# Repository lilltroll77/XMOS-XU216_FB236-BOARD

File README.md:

# XMOS-XU216_FB236-BOARD
### XMOS XU216-FB236 BOARD made in KiCad
**Current status: In DEVELOPMENT**

A 100 x 100 mm 4 layer PCB based on the XMOS XU216 FB236 chip. PCB can be cascaded during development with full JTAG support, and then be used as a galvanic isolated network without JTAG.\
[Schematic as pdf](https://github.com/lilltroll77/XMOS-XU216_FB236-BOARD/blob/master/XMOS_XUF216_FB236.pdf)

The wrl file is a Virtual reality modeling language file of the board with components. 
It can be opened in [FreeCad](https://www.freecadweb.org/) with hardware acceleration. 
Software rendereing is not recommended for realtime view.
The parts for the PCB are stored in the shapes3D folder.

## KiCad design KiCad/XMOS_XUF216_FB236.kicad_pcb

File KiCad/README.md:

The library for the board should be included in the file XMOS_XUF216_FB236-cache.lib\
To view all 3D parts, you might need to add an alias in the KiCad "3D Search Path Configuration" window\
Alias = vrml\
Path = The path to the shapes3D folder on your local machine. (After you have cloned this project)

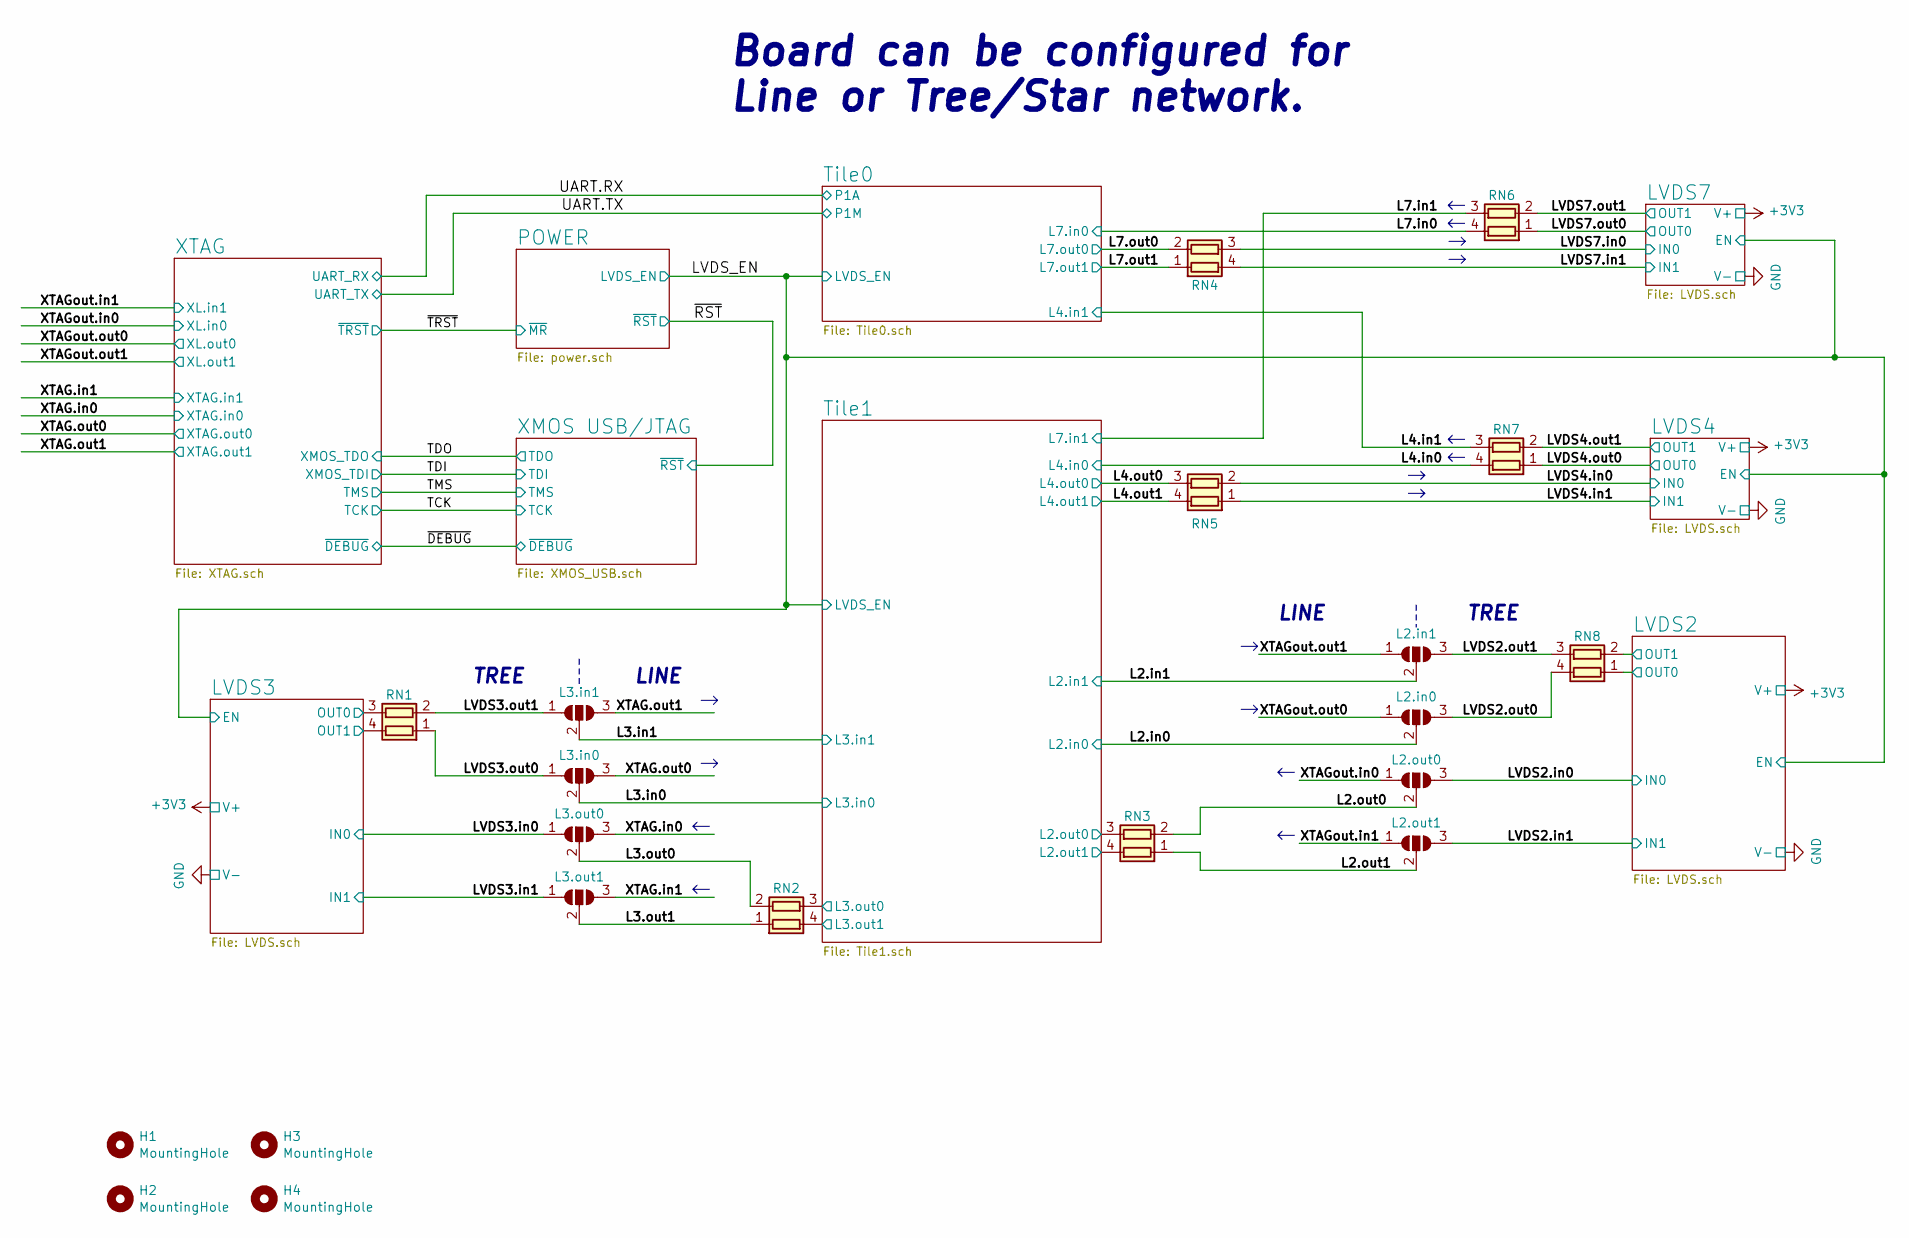
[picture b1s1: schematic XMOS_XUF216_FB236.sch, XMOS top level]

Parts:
H1, H2, H3, H4: MountingHole; MountingHole_3.2mm_M3
JP1: L3.in1; SolderJumper-3_P1.3mm_Open_RoundedPad1.0x1.5mm_NumberLabels
JP2: L3.in0; SolderJumper-3_P1.3mm_Open_RoundedPad1.0x1.5mm_NumberLabels
JP3: L3.out0; SolderJumper-3_P1.3mm_Open_RoundedPad1.0x1.5mm_NumberLabels
JP4: L3.out1; SolderJumper-3_P1.3mm_Open_RoundedPad1.0x1.5mm_NumberLabels
JP5: L2.in1; SolderJumper-3_P1.3mm_Open_RoundedPad1.0x1.5mm_NumberLabels
JP6: L2.in0; SolderJumper-3_P1.3mm_Open_RoundedPad1.0x1.5mm_NumberLabels
JP7: L2.out0; SolderJumper-3_P1.3mm_Open_RoundedPad1.0x1.5mm_NumberLabels
JP8: L2.out1; SolderJumper-3_P1.3mm_Open_RoundedPad1.0x1.5mm_NumberLabels
RN1, RN2, RN3, RN4, RN5, RN6, RN7, RN8: R_Pack02; R_Array_Convex_2x0402

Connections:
/L2.in0: JP6.2 (C); also elsewhere on the board
/L2.in1: JP5.2 (C); also elsewhere on the board
/L2.out0: JP7.2 (C), RN3.2 (R2.1)
/L2.out1: JP8.2 (C), RN3.1 (R1.1)
/L3.in0: JP2.2 (C); also elsewhere on the board
/L3.in1: JP1.2 (C); also elsewhere on the board
/L3.out0: JP3.2 (C), RN2.2 (R2.1)
/L3.out1: JP4.2 (C), RN2.1 (R1.1)
/L4.in0: RN7.4 (R1.2); also elsewhere on the board
/L4.in1: RN7.3 (R2.2); also elsewhere on the board
/L4.out0: RN5.3 (R2.2); also elsewhere on the board
/L4.out1: RN5.4 (R1.2); also elsewhere on the board
/L7.in0: RN6.4 (R1.2); also elsewhere on the board
/L7.in1: RN6.3 (R2.2); also elsewhere on the board
/L7.out0: RN4.2 (R2.1); also elsewhere on the board
/L7.out1: RN4.1 (R1.1); also elsewhere on the board
/LVDS2.in0: JP7.3 (B); also elsewhere on the board
/LVDS2.in1: JP8.3 (B); also elsewhere on the board
/LVDS2.out0: JP6.3 (B), RN8.4 (R1.2)
/LVDS2.out1: JP5.3 (B), RN8.3 (R2.2)
/LVDS2/OUT0: RN8.1 (R1.1); also elsewhere on the board
/LVDS2/OUT1: RN8.2 (R2.1); also elsewhere on the board
/LVDS3.in0: JP3.1 (A); also elsewhere on the board
/LVDS3.in1: JP4.1 (A); also elsewhere on the board
/LVDS3.out0: JP2.1 (A), RN1.1 (R1.1)
/LVDS3.out1: JP1.1 (A), RN1.2 (R2.1)
/LVDS3/OUT0: RN1.3 (R2.2); also elsewhere on the board
/LVDS3/OUT1: RN1.4 (R1.2); also elsewhere on the board
/LVDS4.in0: RN5.2 (R2.1); also elsewhere on the board
/LVDS4.in1: RN5.1 (R1.1); also elsewhere on the board
/LVDS4.out0: RN7.1 (R1.1); also elsewhere on the board
/LVDS4.out1: RN7.2 (R2.1); also elsewhere on the board
/LVDS7.in0: RN4.3 (R2.2); also elsewhere on the board
/LVDS7.in1: RN4.4 (R1.2); also elsewhere on the board
/LVDS7.out0: RN6.1 (R1.1); also elsewhere on the board
/LVDS7.out1: RN6.2 (R2.1); also elsewhere on the board
/Tile1/L2.out0: RN3.3 (R2.2); also elsewhere on the board
/Tile1/L2.out1: RN3.4 (R1.2); also elsewhere on the board
/Tile1/L3.out0: RN2.3 (R2.2); also elsewhere on the board
/Tile1/L3.out1: RN2.4 (R1.2); also elsewhere on the board
/XTAG.in0: JP3.3 (B); also elsewhere on the board
/XTAG.in1: JP4.3 (B); also elsewhere on the board
/XTAG.out0: JP2.3 (B); also elsewhere on the board
/XTAG.out1: JP1.3 (B); also elsewhere on the board
/XTAGout.in0: JP7.1 (A); also elsewhere on the board
/XTAGout.in1: JP8.1 (A); also elsewhere on the board
/XTAGout.out0: JP6.1 (A); also elsewhere on the board
/XTAGout.out1: JP5.1 (A); also elsewhere on the board

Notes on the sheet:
Board can be configured for Line or Tree/Star network.
TREE
LINE

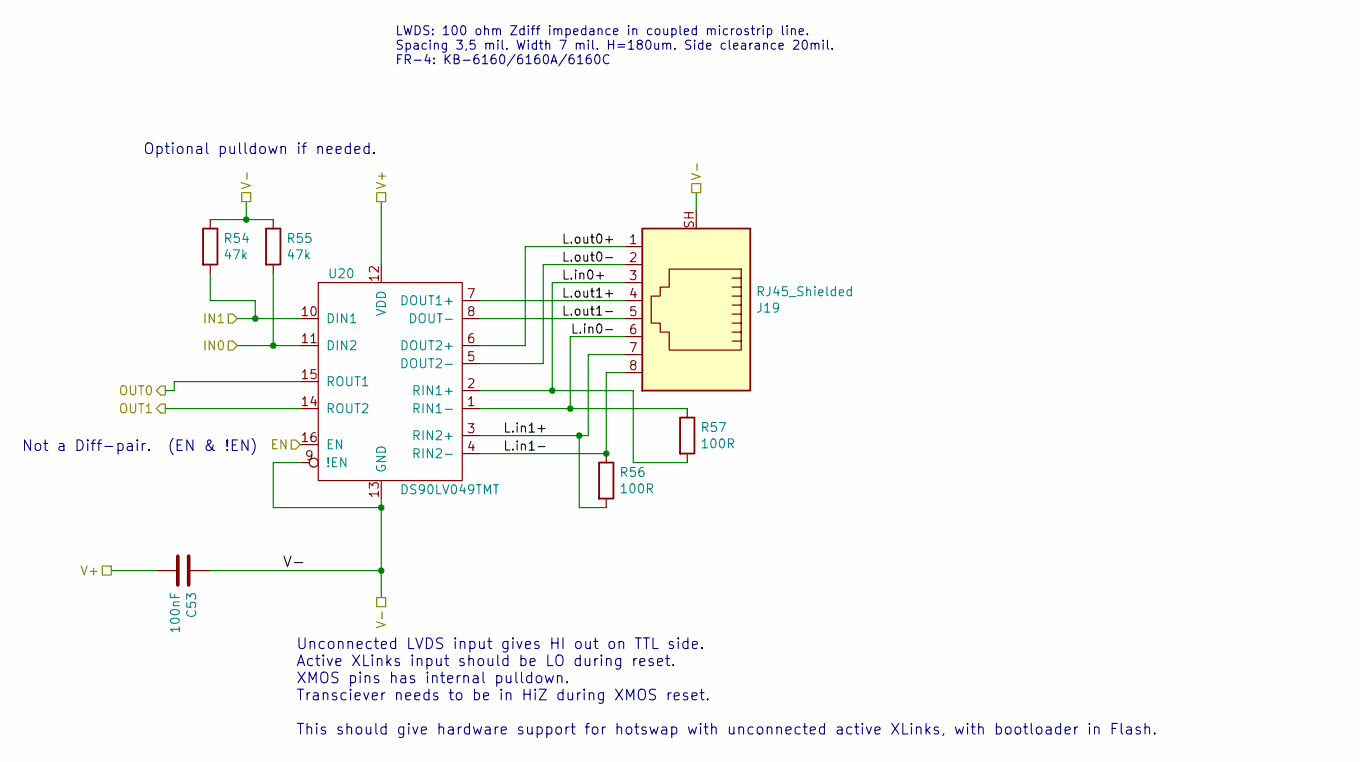
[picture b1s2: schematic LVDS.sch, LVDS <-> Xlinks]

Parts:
C1: 100nF; C_0603_1608Metric_Pad1.05x0.95mm_HandSolder
J1: RJ45_Shielded; RJ45_Amphenol_RJHSE5380
R1, R2: 47k; R_0402_1005Metric
R3, R4: 100R; R_0402_1005Metric
U1: DS90LV049TMT; TSSOP-16_4.4x5mm_P0.65mm

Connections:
/LVDS7.in0: R2.2, U1.11 (DIN2); also elsewhere on the board
/LVDS7.in1: R1.2, U1.10 (DIN1); also elsewhere on the board
/LVDS7.out0: U1.15 (ROUT1); also elsewhere on the board
/LVDS7.out1: U1.14 (ROUT2); also elsewhere on the board
/LVDS7/L.in0+: J1.3, R4.2, U1.2 (RIN1+)
/LVDS7/L.in0-: J1.6, R4.1, U1.1 (RIN1-)
/LVDS7/L.in1+: J1.7, R3.2, U1.3 (RIN2+)
/LVDS7/L.in1-: J1.8, R3.1, U1.4 (RIN2-)
/LVDS7/L.out0+: J1.1, U1.6 (DOUT2+)
/LVDS7/L.out0-: J1.2, U1.5 (DOUT2-)
/LVDS7/L.out1+: J1.4, U1.7 (DOUT1+)
/LVDS7/L.out1-: J1.5, U1.8 (DOUT-)
/LVDS_EN: U1.16 (EN); also elsewhere on the board
GND: C1.1, J1.SH, R1.1, R2.1, U1.9 (!EN), U1.13 (GND); also elsewhere on the board

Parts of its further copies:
C15, C46, C47, C48, C49, C50, C53: 100nF; C_0603_1608Metric_Pad1.05x0.95mm_HandSolder
J4, J13, J14, J16, J17, J18, J19: RJ45_Shielded; RJ45_Amphenol_RJHSE5380
R15, R16, R31, R32, R35, R36, R42, R43, R46, R47, R50, R51, R54, R55: 47k; R_0402_1005Metric
R17, R18, R33, R34, R37, R38, R44, R45, R48, R49, R52, R53, R56, R57: 100R; R_0402_1005Metric
U8, U14, U15, U16, U17, U18, U20: DS90LV049TMT; TSSOP-16_4.4x5mm_P0.65mm

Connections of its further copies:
+3.3VP: C46.2, C50.2, U14.12 (VDD), U14.16 (EN), U18.12 (VDD), U18.16 (EN); also elsewhere on the board
/LVDS2.in0: R16.2, U8.11 (DIN2); also elsewhere on the board
/LVDS2.in1: R15.2, U8.10 (DIN1); also elsewhere on the board
/LVDS2/L.in0+: J4.3, R18.2, U8.2 (RIN1+)
/LVDS2/L.in0-: J4.6, R18.1, U8.1 (RIN1-)
/LVDS2/L.in1+: J4.7, R17.2, U8.3 (RIN2+)
/LVDS2/L.in1-: J4.8, R17.1, U8.4 (RIN2-)
/LVDS2/L.out0+: J4.1, U8.6 (DOUT2+)
/LVDS2/L.out0-: J4.2, U8.5 (DOUT2-)
/LVDS2/L.out1+: J4.4, U8.7 (DOUT1+)
/LVDS2/L.out1-: J4.5, U8.8 (DOUT-)
/LVDS2/OUT0: U8.15 (ROUT1); also elsewhere on the board
/LVDS2/OUT1: U8.14 (ROUT2); also elsewhere on the board
/LVDS3.in0: R55.2, U20.11 (DIN2); also elsewhere on the board
/LVDS3.in1: R54.2, U20.10 (DIN1); also elsewhere on the board
/LVDS3/L.in0+: J19.3, R57.2, U20.2 (RIN1+)
/LVDS3/L.in0-: J19.6, R57.1, U20.1 (RIN1-)
/LVDS3/L.in1+: J19.7, R56.2, U20.3 (RIN2+)
/LVDS3/L.in1-: J19.8, R56.1, U20.4 (RIN2-)
/LVDS3/L.out0+: J19.1, U20.6 (DOUT2+)
/LVDS3/L.out0-: J19.2, U20.5 (DOUT2-)
/LVDS3/L.out1+: J19.4, U20.7 (DOUT1+)
/LVDS3/L.out1-: J19.5, U20.8 (DOUT-)
/LVDS3/OUT0: U20.15 (ROUT1); also elsewhere on the board
/LVDS3/OUT1: U20.14 (ROUT2); also elsewhere on the board
/LVDS4.in0: R36.2, U15.11 (DIN2); also elsewhere on the board
/LVDS4.in1: R35.2, U15.10 (DIN1); also elsewhere on the board
/LVDS4.out0: U15.15 (ROUT1); also elsewhere on the board
/LVDS4.out1: U15.14 (ROUT2); also elsewhere on the board
/LVDS4/L.in0+: J14.3, R38.2, U15.2 (RIN1+)
/LVDS4/L.in0-: J14.6, R38.1, U15.1 (RIN1-)
/LVDS4/L.in1+: J14.7, R37.2, U15.3 (RIN2+)
/LVDS4/L.in1-: J14.8, R37.1, U15.4 (RIN2-)
/LVDS4/L.out0+: J14.1, U15.6 (DOUT2+)
/LVDS4/L.out0-: J14.2, U15.5 (DOUT2-)
/LVDS4/L.out1+: J14.4, U15.7 (DOUT1+)
/LVDS4/L.out1-: J14.5, U15.8 (DOUT-)
/LVDS_EN: U8.16 (EN), U15.16 (EN), U16.16 (EN), U17.16 (EN), U20.16 (EN); also elsewhere on the board
/Tile0/LVDS0.in0: R51.2, U18.11 (DIN2); also elsewhere on the board
/Tile0/LVDS0.in1: R50.2, U18.10 (DIN1); also elsewhere on the board
/Tile0/LVDS0.out0: U18.15 (ROUT1); also elsewhere on the board
/Tile0/LVDS0.out1: U18.14 (ROUT2); also elsewhere on the board
/Tile0/LVDS0/L.in0+: J18.3, R53.2, U18.2 (RIN1+)
/Tile0/LVDS0/L.in0-: J18.6, R53.1, U18.1 (RIN1-)
/Tile0/LVDS0/L.in1+: J18.7, R52.2, U18.3 (RIN2+)
/Tile0/LVDS0/L.in1-: J18.8, R52.1, U18.4 (RIN2-)
/Tile0/LVDS0/L.out0+: J18.1, U18.6 (DOUT2+)
/Tile0/LVDS0/L.out0-: J18.2, U18.5 (DOUT2-)
/Tile0/LVDS0/L.out1+: J18.4, U18.7 (DOUT1+)
/Tile0/LVDS0/L.out1-: J18.5, U18.8 (DOUT-)
/Tile0/LVDS5.in0: R47.2, U17.11 (DIN2); also elsewhere on the board
/Tile0/LVDS5.in1: R46.2, U17.10 (DIN1); also elsewhere on the board
/Tile0/LVDS5.out0: U17.15 (ROUT1); also elsewhere on the board
/Tile0/LVDS5.out1: U17.14 (ROUT2); also elsewhere on the board
/Tile0/LVDS5/L.in0+: J17.3, R49.2, U17.2 (RIN1+)
/Tile0/LVDS5/L.in0-: J17.6, R49.1, U17.1 (RIN1-)
/Tile0/LVDS5/L.in1+: J17.7, R48.2, U17.3 (RIN2+)
/Tile0/LVDS5/L.in1-: J17.8, R48.1, U17.4 (RIN2-)
/Tile0/LVDS5/L.out0+: J17.1, U17.6 (DOUT2+)
/Tile0/LVDS5/L.out0-: J17.2, U17.5 (DOUT2-)
/Tile0/LVDS5/L.out1+: J17.4, U17.7 (DOUT1+)
/Tile0/LVDS5/L.out1-: J17.5, U17.8 (DOUT-)
/Tile0/LVDS6.in0: R43.2, U16.11 (DIN2); also elsewhere on the board
/Tile0/LVDS6.in1: R42.2, U16.10 (DIN1); also elsewhere on the board
/Tile0/LVDS6.out0: U16.15 (ROUT1); also elsewhere on the board
/Tile0/LVDS6.out1: U16.14 (ROUT2); also elsewhere on the board
/Tile0/LVDS6/L.in0+: J16.3, R45.2, U16.2 (RIN1+)
/Tile0/LVDS6/L.in0-: J16.6, R45.1, U16.1 (RIN1-)
/Tile0/LVDS6/L.in1+: J16.7, R44.2, U16.3 (RIN2+)
/Tile0/LVDS6/L.in1-: J16.8, R44.1, U16.4 (RIN2-)
/Tile0/LVDS6/L.out0+: J16.1, U16.6 (DOUT2+)
/Tile0/LVDS6/L.out0-: J16.2, U16.5 (DOUT2-)
/Tile0/LVDS6/L.out1+: J16.4, U16.7 (DOUT1+)
/Tile0/LVDS6/L.out1-: J16.5, U16.8 (DOUT-)
/Tile1/LVDS1/L.in0+: J13.3, R34.2, U14.2 (RIN1+)
/Tile1/LVDS1/L.in0-: J13.6, R34.1, U14.1 (RIN1-)
/Tile1/LVDS1/L.in1+: J13.7, R33.2, U14.3 (RIN2+)
/Tile1/LVDS1/L.in1-: J13.8, R33.1, U14.4 (RIN2-)
/Tile1/LVDS1/L.out0+: J13.1, U14.6 (DOUT2+)
/Tile1/LVDS1/L.out0-: J13.2, U14.5 (DOUT2-)
/Tile1/LVDS1/L.out1+: J13.4, U14.7 (DOUT1+)
/Tile1/LVDS1/L.out1-: J13.5, U14.8 (DOUT-)
/Tile1/LVDS.in0: R32.2, U14.11 (DIN2); also elsewhere on the board
/Tile1/LVDS.in1: R31.2, U14.10 (DIN1); also elsewhere on the board
/Tile1/LVDS.out0: U14.15 (ROUT1); also elsewhere on the board
/Tile1/LVDS.out1: U14.14 (ROUT2); also elsewhere on the board
GND: C15.1, C47.1, C48.1, C49.1, C53.1, J4.SH, J14.SH, J16.SH, J17.SH, J19.SH, R15.1, R16.1, R35.1, R36.1, R42.1, R43.1, R46.1, R47.1, R54.1, R55.1, U8.9 (!EN), U8.13 (GND), U15.9 (!EN), U15.13 (GND), U16.9 (!EN), U16.13 (GND), U17.9 (!EN), U17.13 (GND), U20.9 (!EN), U20.13 (GND); also elsewhere on the board
GNDD: C46.1, C50.1, J13.SH, J18.SH, R31.1, R32.1, R50.1, R51.1, U14.9 (!EN), U14.13 (GND), U18.9 (!EN), U18.13 (GND); also elsewhere on the board

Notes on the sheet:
Unconnected LVDS input gives HI out on TTL side. Active XLinks input should be LO during reset. XMOS pins has internal pulldown. Transciever needs to be in HiZ during XMOS reset. This should give hardware support for hotswap with unconnected active XLinks, with bootloader in Flash.
Optional pulldown if needed.
Not a Diff-pair. (EN & !EN)
LWDS: 100 ohm Zdiff impedance in coupled microstrip line. Spacing 3,5 mil. Width 7 mil. H=180um. Side clearance 20mil. FR-4: KB-6160/6160A/6160C

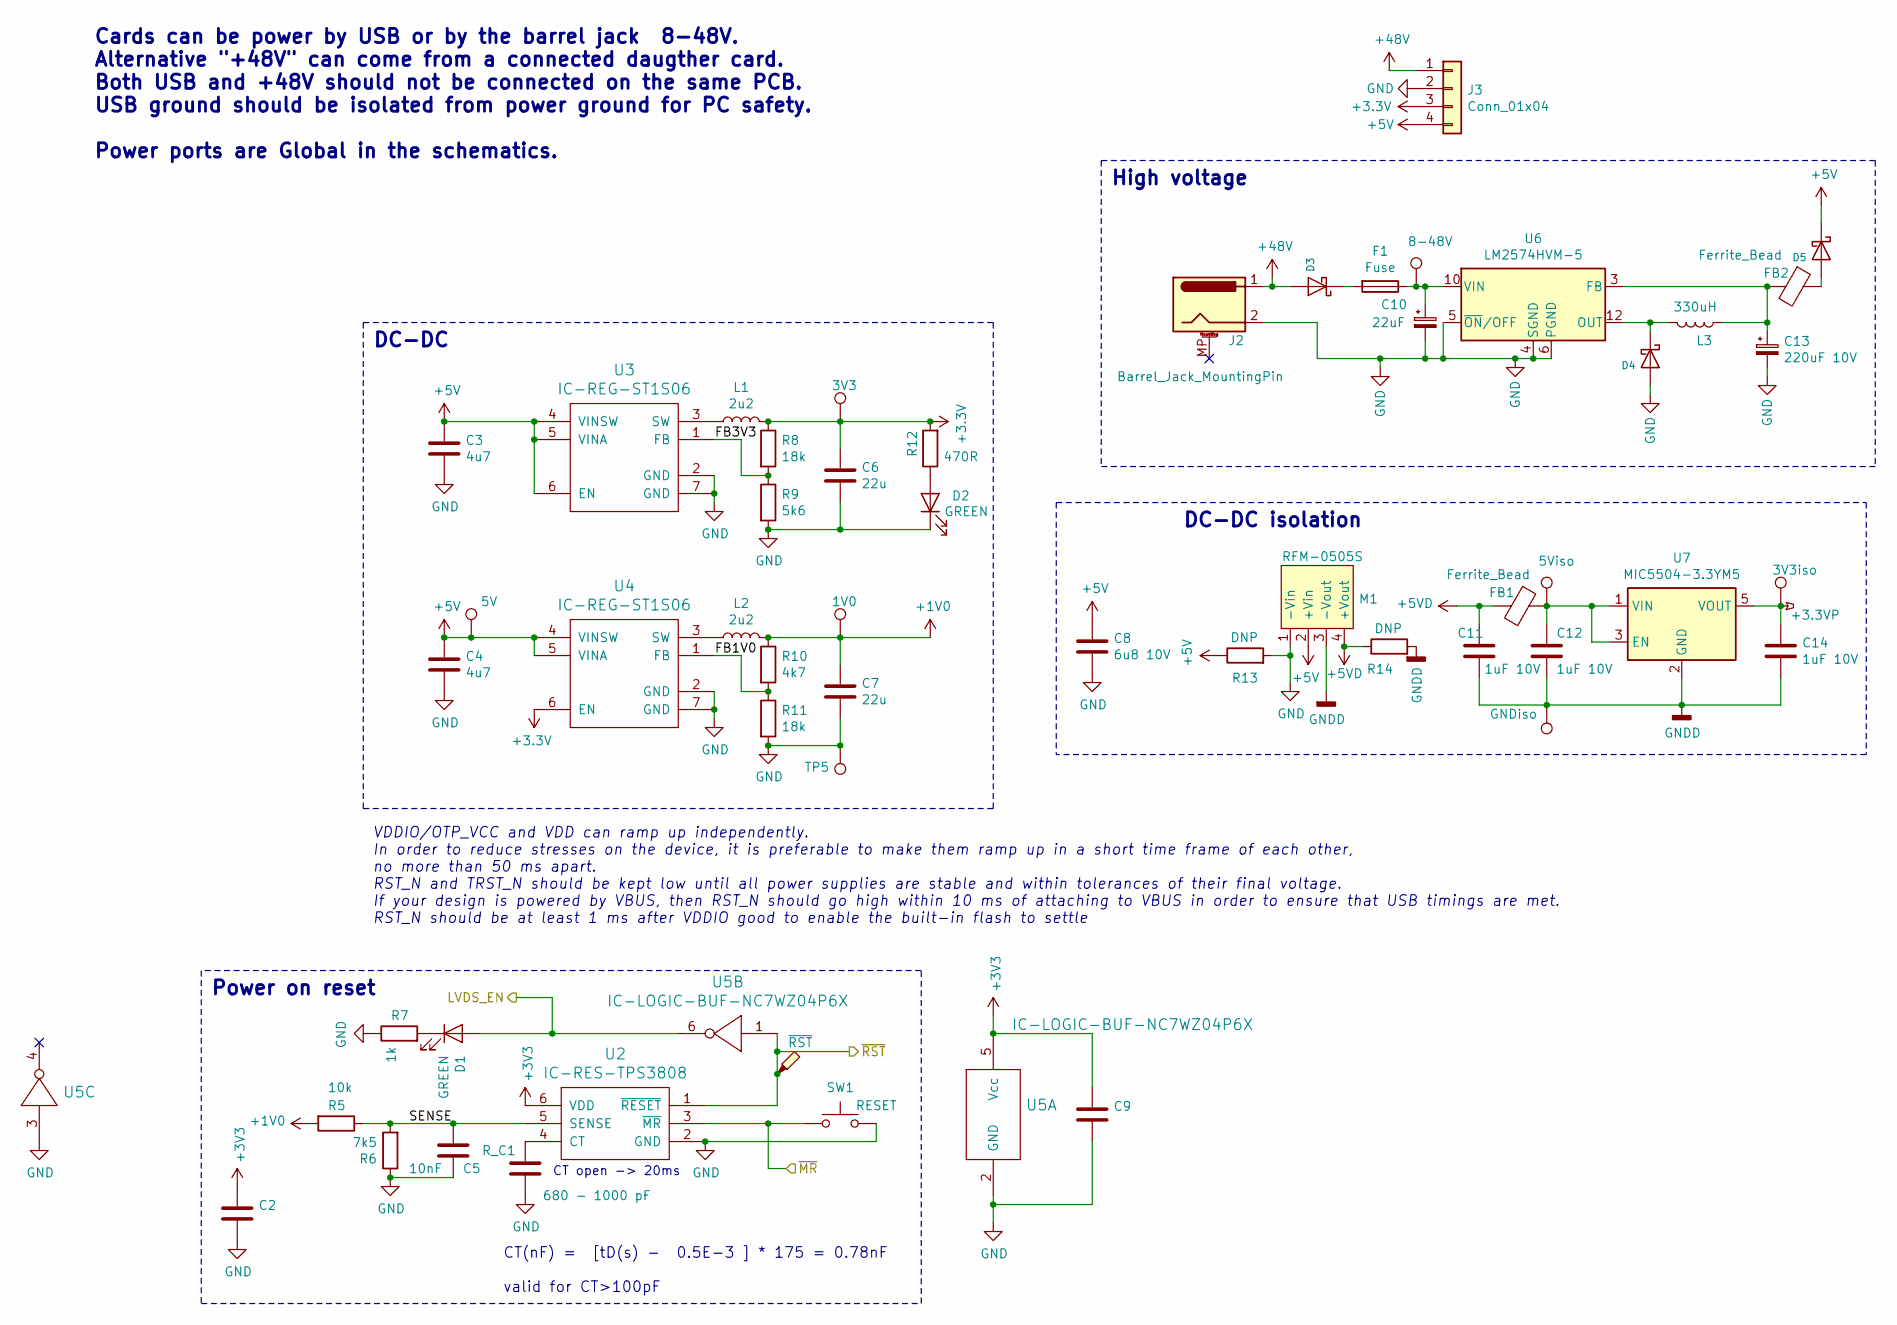
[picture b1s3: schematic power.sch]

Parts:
C2, C9: C; C_0603_1608Metric_Pad1.05x0.95mm_HandSolder
C3, C4: 4u7; C_0805_2012Metric_Pad1.15x1.40mm_HandSolder
C5: 10nF; C_0603_1608Metric
C6, C7: 22u; C_0805_2012Metric_Pad1.15x1.40mm_HandSolder
C8: 6u8 10V; C_0603_1608Metric_Pad1.05x0.95mm_HandSolder
C10: 22uF; C_Radial_D6.3mm_H11.0mm_P2.50mm; Part Number ESK226M100AE3AA
C11, C12, C14: 1uF 10V; C_0603_1608Metric_Pad1.05x0.95mm_HandSolder
C13: 220uF 10V; C_Radial_D6.3mm_H11.0mm_P2.50mm; Part Number 860040273002
D1, D2: GREEN; LED_0603_1608Metric_Pad1.05x0.95mm_HandSolder
D3, D5: SCHOTTKY_DIODE; D_SOD-123; Part Number MUR1100ERLG
D4: SCHOTTKY_DIODE; D_SOD-123F; Part Number MUR1100ERLG
F1: Fuse; Fuse_0805_2012Metric_Pad1.15x1.40mm_HandSolder
FB1: Ferrite_Bead; L_0603_1608Metric_Pad1.05x0.95mm_HandSolder
FB2: Ferrite_Bead; L_0805_2012Metric_Pad1.15x1.40mm_HandSolder
J2: Barrel_Jack_MountingPin; BarrelJack_Horizontal
J3: Conn_01x04; PinSocket_1x04_P2.54mm_Vertical
L1, L2: 2u2; L_Taiyo-Yuden_NR-60xx_HandSoldering
L3: 330uH; L_Bourns_SRR1210A
M1: RFM-0505S; RECON RFM DCDC
R5: 10k; R_0603_1608Metric_Pad1.05x0.95mm_HandSolder
R6: 7k5; R_0603_1608Metric_Pad1.05x0.95mm_HandSolder
R7: 1k; R_0603_1608Metric_Pad1.05x0.95mm_HandSolder
R8, R11: 18k; R_0603_1608Metric_Pad1.05x0.95mm_HandSolder
R9: 5k6; R_0603_1608Metric_Pad1.05x0.95mm_HandSolder
R10: 4k7; R_0603_1608Metric_Pad1.05x0.95mm_HandSolder
R12: 470R; R_0603_1608Metric_Pad1.05x0.95mm_HandSolder
R13, R14: DNP; R_0603_1608Metric_Pad1.05x0.95mm_HandSolder
R_C1: 680 - 1000 pF; C_0603_1608Metric_Pad1.05x0.95mm_HandSolder
SW1: RESET; SW_SPST_B3U-1000P
TP1: 5V; TestPoint_Loop_D1.80mm_Drill1.0mm_Beaded
TP2: ~RST; TestPoint_THTPad_2.0x2.0mm_Drill1.0mm
TP3: 3V3; TestPoint_Loop_D1.80mm_Drill1.0mm_Beaded
TP4: 1V0; TestPoint_Loop_D1.80mm_Drill1.0mm_Beaded
TP5: GND; TestPoint_THTPad_1.5x1.5mm_Drill0.7mm
TP6: 8-48V; TestPoint_Loop_D1.80mm_Drill1.0mm_Beaded
TP7: 5Viso; TestPoint_Loop_D1.80mm_Drill1.0mm_Beaded
TP8: GNDiso; TestPoint_THTPad_1.5x1.5mm_Drill0.7mm
TP9: 3V3iso; TestPoint_Loop_D1.80mm_Drill1.0mm_Beaded
U2: IC-RES-TPS3808; SOT-23-6_Handsoldering
U3, U4: IC-REG-ST1S06; DFN-6-1EP_3x3mm_P1mm_EP1.5x2.4mm
U5: IC-LOGIC-BUF-NC7WZ04P6X; SOT-363_SC-70-6_Handsoldering
U6: LM2574HVM-5; SOIC-14W_7.5x9.0mm_P1.27mm
U7: MIC5504-3.3YM5; SOT-23-5

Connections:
+1V0: C7.1, L2.2, R5.2, R10.1, TP4.1; also elsewhere on the board
+3.3VP: C14.1, TP9.1, U7.5 (VOUT); also elsewhere on the board
+5V: C3.1, C4.1, C8.1, D5.1 (K), J3.4, M1.2 (+Vin), R13.1, TP1.1, U3.4 (VINSW), U3.5 (VINA), U3.6 (EN), U4.4 (VINSW), U4.5 (VINA); also elsewhere on the board
+5VD: C11.1, FB1.2, M1.4 (+Vout), R14.1
+48V: D3.2 (A), J2.1, J3.1
/LVDS_EN: D1.2 (A), U5.6; also elsewhere on the board
/POWER/FB1V0: R10.2, R11.1, U4.1 (FB)
/POWER/FB3V3: R8.2, R9.1, U3.1 (FB)
/POWER/SENSE: C5.1, R5.1, R6.2, U2.5 (SENSE)
/~RST: TP2.1, U2.1 (~RESET), U5.1; also elsewhere on the board
/~TRST: SW1.1, U2.3 (~MR); also elsewhere on the board
GND: C2.2, C3.2, C4.2, C5.2, C6.2, C7.2, C8.2, C9.2, C10.2, C13.2, D2.1 (K), D4.2 (A), J2.2, J3.2, M1.1 (-Vin), R6.1, R7.1, R9.2, R11.2, R13.2, R_C1.1, SW1.2, TP5.1, U2.2 (GND), U3.2 (GND), U3.7 (GND), U4.2 (GND), U4.7 (GND), U5.2 (GND), U5.3, U6.4 (SGND), U6.5 (~ON~/OFF), U6.6 (PGND); also elsewhere on the board
GNDD: C11.2, C12.2, C14.2, M1.3 (-Vout), R14.2, TP8.1, U7.2 (GND); also elsewhere on the board
unnamed: C10.1, F1.1, TP6.1, U6.10 (VIN)
unnamed: C12.1, FB1.1, TP7.1, U7.1 (VIN), U7.3 (EN)
unnamed: C13.1, FB2.2, L3.1, U6.3 (FB)
unnamed: D1.1 (K), R7.2
unnamed: D2.2 (A), R12.1
unnamed: D3.1 (K), F1.2
unnamed: D4.1 (K), L3.2, U6.12 (OUT)
unnamed: D5.2 (A), FB2.1
unnamed: L1.1, U3.3 (SW)
unnamed: L2.1, U4.3 (SW)
unnamed: R_C1.2, U2.4 (CT)

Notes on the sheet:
High voltage
DC-DC isolation
DC-DC
Cards can be power by USB or by the barrel jack 8-48V. Alternative "+48V" can come from a connected daugther card. Both USB and +48V should not be connected on the same PCB. USB ground should be isolated from power ground for PC safety. Power ports are Global in the schematics.
VDDIO/OTP_VCC and VDD can ramp up independently. In order to reduce stresses on the device, it is preferable to make them ramp up in a short time frame of each other, no more than 50 ms apart. RST_N and TRST_N should be kept low until all power supplies are stable and within tolerances of their fin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
CT open -> 20ms
Power on reset
CT(nF) = [tD(s) - 0.5E-3 ] * 175 = 0.78nF valid for CT>100pF

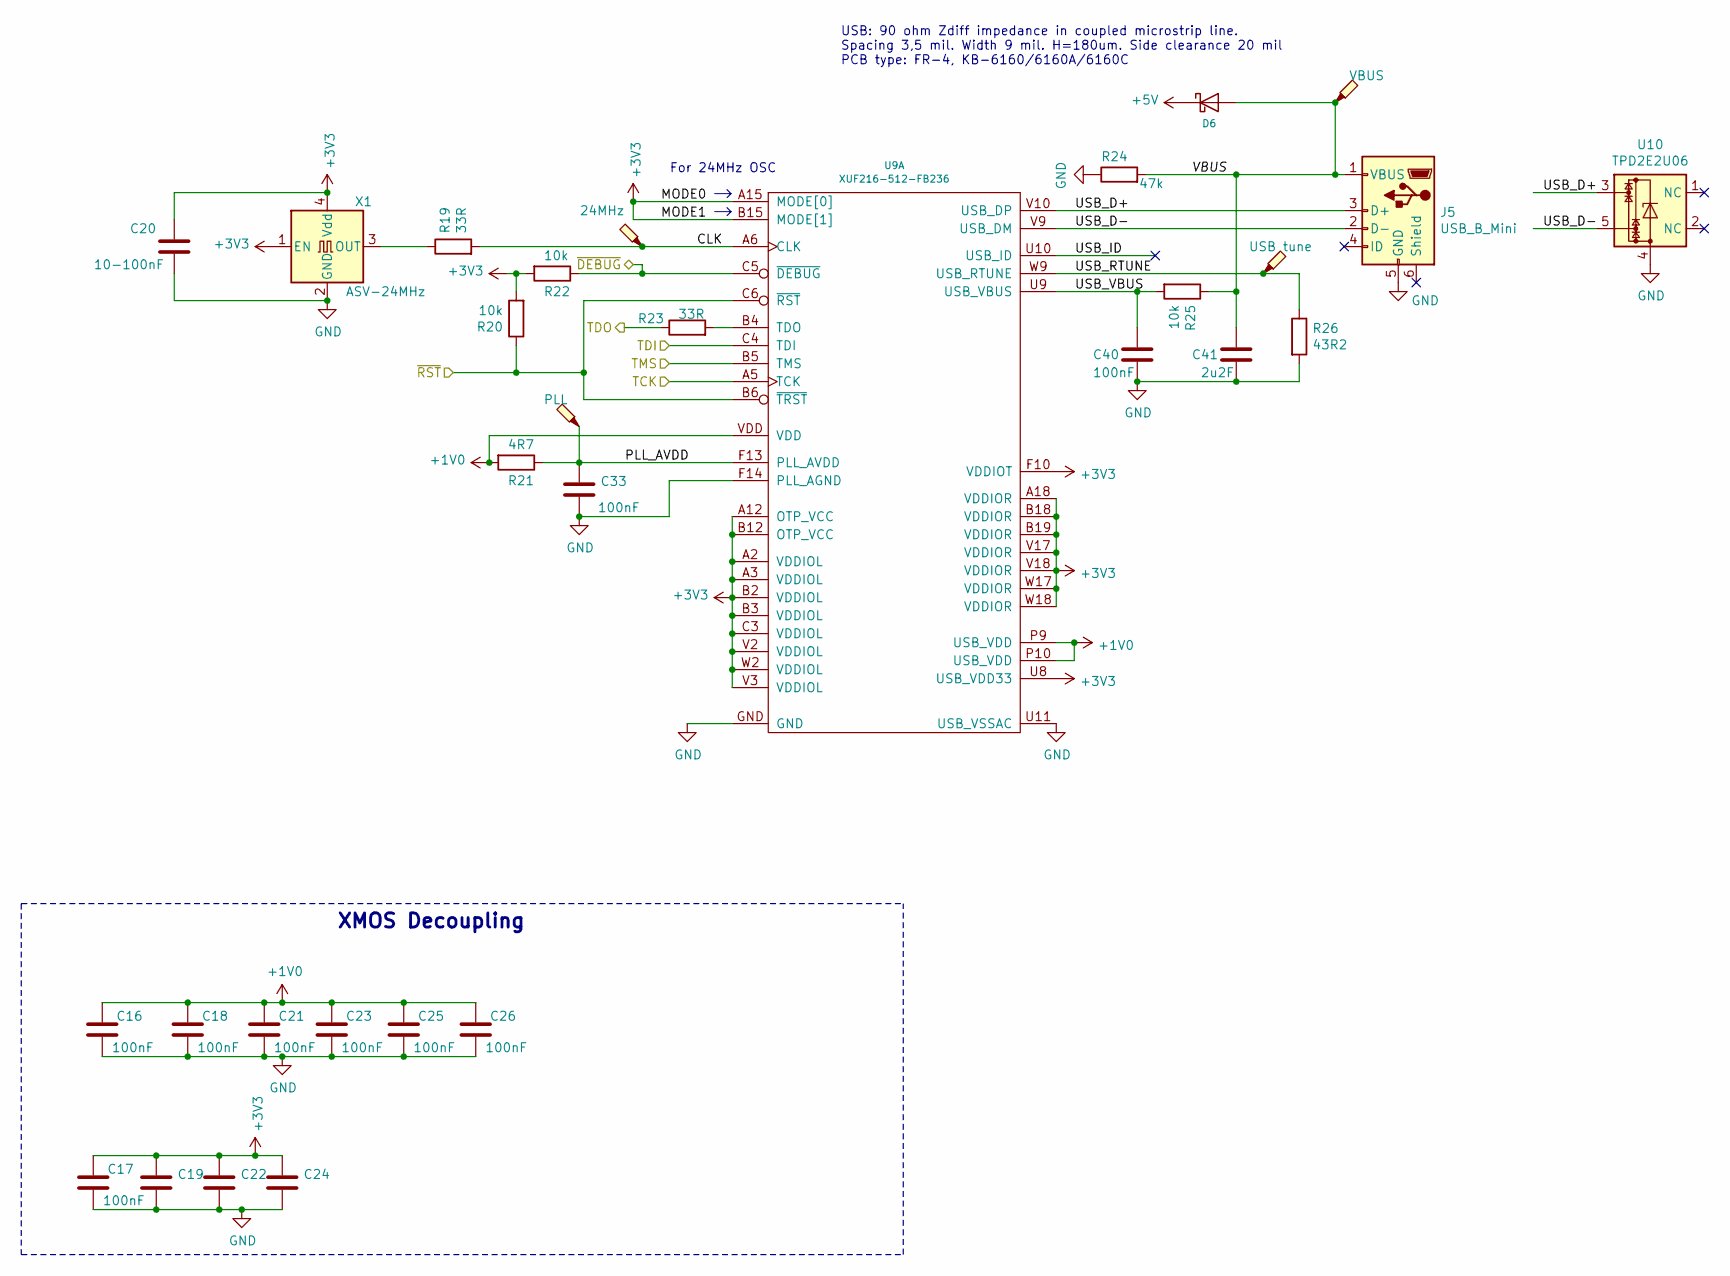
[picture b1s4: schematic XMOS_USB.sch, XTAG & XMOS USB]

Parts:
C16, C18, C21, C23, C25, C26, C33, C40: 100nF; C_0402_1005Metric
C17: 100nF; C_0603_1608Metric_Pad1.05x0.95mm_HandSolder
C19, C22, C24: C; C_0603_1608Metric_Pad1.05x0.95mm_HandSolder
C20: 10-100nF; C_0402_1005Metric
C41: 2u2F; C_0402_1005Metric
D6: SCHOTTKY_DIODE; D_SOD-123
J5: USB_B_Mini; USB_Micro-B_Molex-105017-0001
R19, R23: 33R; R_0603_1608Metric_Pad1.05x0.95mm_HandSolder
R20, R22, R25: 10k; R_0603_1608Metric_Pad1.05x0.95mm_HandSolder
R21: 4R7; R_0603_1608Metric_Pad1.05x0.95mm_HandSolder
R24: 47k; R_0603_1608Metric_Pad1.05x0.95mm_HandSolder
R26: 43R2; R_0603_1608Metric_Pad1.05x0.95mm_HandSolder
TP10: PLL; TestPoint_Pad_0.6x0.6mm
TP11: 24MHz; TestPoint_Pad_0.6x0.6mm
TP12: USB tune; TestPoint_Pad_0.6x0.6mm
TP13: VBUS; TestPoint_Pad_1.0x1.0mm
U9: XUF216-512-FB236; BGA_236
U10: TPD2E2U06; SOT-553
X1: ASV-24MHz; Oscillator_SMD_SeikoEpson_SG210-4Pin_2.5x2.0mm

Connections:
+1V0: C16.1, C18.1, C21.1, C23.1, C25.1, C26.1, R21.2, U9.P9 (USB_VDD), U9.P10 (USB_VDD), U9.VDD; also elsewhere on the board
+5V: D6.1 (K); also elsewhere on the board
/TCK: U9.A5 (TCK); also elsewhere on the board
/TDI: U9.C4 (TDI); also elsewhere on the board
/TDO: R23.1; also elsewhere on the board
/TMS: U9.B5 (TMS); also elsewhere on the board
/XMOS USB/JTAG/CLK: R19.2, TP11.1, U9.A6 (CLK)
/XMOS USB/JTAG/PLL_AVDD: C33.1, R21.1, TP10.1, U9.F13 (PLL_AVDD)
/XMOS USB/JTAG/USB_D+: J5.3 (D+), U9.V10 (USB_DP), U10.3
/XMOS USB/JTAG/USB_D-: J5.2 (D-), U9.V9 (USB_DM), U10.5
/XMOS USB/JTAG/USB_ID: U9.U10 (USB_ID)
/XMOS USB/JTAG/USB_RTUNE: R26.1, TP12.1, U9.W9 (USB_RTUNE)
/XMOS USB/JTAG/USB_VBUS: C40.1, R25.2, U9.U9 (USB_VBUS)
/XMOS USB/JTAG/VBUS: C41.1, D6.2 (A), J5.1 (VBUS), R24.2, R25.1, TP13.1
/~DEBUG: R22.1, U9.C5 (~DEBUG); also elsewhere on the board
/~RST: R20.1, U9.B6 (~TRST), U9.C6 (~RST); also elsewhere on the board
GND: C16.2, C17.2, C18.2, C19.2, C20.2, C21.2, C22.2, C23.2, C24.2, C25.2, C26.2, C33.2, C40.2, C41.2, J5.5 (GND), R24.1, R26.2, U9.F14 (PLL_AGND), U9.GND, U9.U11 (USB_VSSAC), U10.4, X1.2 (GND); also elsewhere on the board
unnamed: R19.1, X1.3 (OUT)
unnamed: R23.2, U9.B4 (TDO)

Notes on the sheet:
For 24MHz OSC
XMOS Decoupling
USB: 90 ohm Zdiff impedance in coupled microstrip line. Spacing 3,5 mil. Width 9 mil. H=180um. Side clearance 20 mil PCB type: FR-4, KB-6160/6160A/6160C

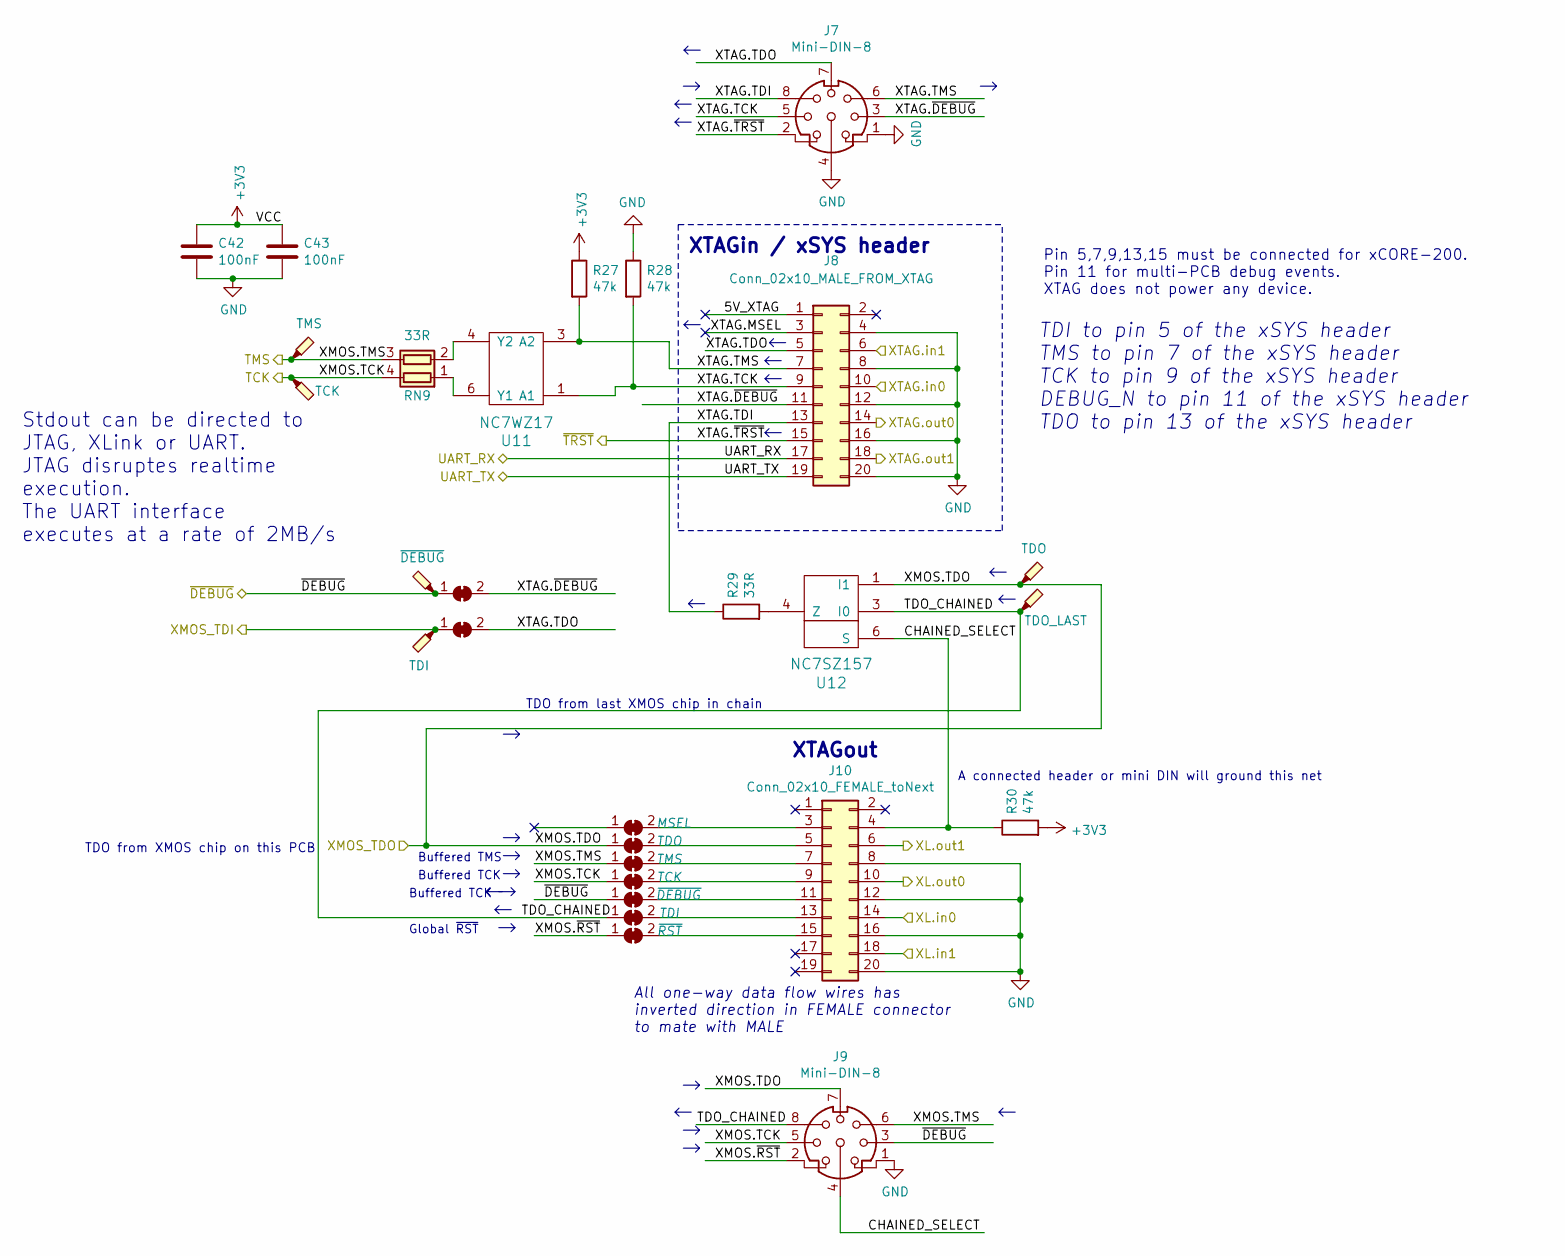
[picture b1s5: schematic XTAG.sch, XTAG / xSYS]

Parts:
C42, C43: 100nF; C_0603_1608Metric_Pad1.05x0.95mm_HandSolder
J7, J9: Mini-DIN-8; MDC-278
J8: Conn_02x10_MALE_FROM_XTAG; IDC-Header_2x10_P2.54mm_Horizontal
J10: Conn_02x10_FEMALE_toNext; PinSocket_2x10_P2.54mm_Horizontal; Part Number SFH11-PBPC-D10-RA-BK
JP9, JP15: ~DEBUG; SolderJumper-2_P1.3mm_Bridged_RoundedPad1.0x1.5mm
JP10, JP12: TDO; SolderJumper-2_P1.3mm_Bridged_RoundedPad1.0x1.5mm
JP11: MSEL; SolderJumper-2_P1.3mm_Bridged_RoundedPad1.0x1.5mm
JP13: TMS; SolderJumper-2_P1.3mm_Bridged_RoundedPad1.0x1.5mm
JP14: TCK; SolderJumper-2_P1.3mm_Bridged_RoundedPad1.0x1.5mm
JP16: TDI; SolderJumper-2_P1.3mm_Bridged_RoundedPad1.0x1.5mm
JP17: ~RST; SolderJumper-2_P1.3mm_Bridged_RoundedPad1.0x1.5mm
R27, R28, R30: 47k; R_0603_1608Metric_Pad1.05x0.95mm_HandSolder
R29: 33R; R_0603_1608Metric_Pad1.05x0.95mm_HandSolder
RN9: 33R; R_Array_Convex_2x0402
TP14: TMS; TestPoint_THTPad_1.5x1.5mm_Drill0.7mm
TP15: TCK; TestPoint_THTPad_1.5x1.5mm_Drill0.7mm
TP16: ~DEBUG; TestPoint_THTPad_1.5x1.5mm_Drill0.7mm
TP17: TDI; TestPoint_THTPad_1.5x1.5mm_Drill0.7mm
TP18: TDO; TestPoint_THTPad_1.5x1.5mm_Drill0.7mm
TP19: TDO_LAST; TestPoint_THTPad_1.5x1.5mm_Drill0.7mm
U11: NC7WZ17; SOT-363_SC-70-6_Handsoldering
U12: NC7SZ157; SOT-363_SC-70-6_Handsoldering

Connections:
/TCK: J9.5, JP14.1 (A), RN9.4 (R1.2), TP15.1; also elsewhere on the board
/TDI: JP10.1 (A), TP17.1; also elsewhere on the board
/TDO: J9.7, JP12.1 (A), TP18.1, U12.1 (I1); also elsewhere on the board
/TMS: J9.6, JP13.1 (A), RN9.3 (R2.2), TP14.1; also elsewhere on the board
/UART.RX: J8.17; also elsewhere on the board
/UART.TX: J8.19; also elsewhere on the board
/XTAG.in0: J8.10; also elsewhere on the board
/XTAG.in1: J8.6; also elsewhere on the board
/XTAG.out0: J8.14; also elsewhere on the board
/XTAG.out1: J8.18; also elsewhere on the board
/XTAG/5V_XTAG: J8.1
/XTAG/CHAINED_SELECT: J9.4, J10.4, R30.1, U12.6 (S)
/XTAG/TDO_CHAINED: J9.8, JP16.1 (A), TP19.1, U12.3 (I0)
/XTAG/XMOS.~RST: J9.2, JP17.1 (A)
/XTAG/XTAG.MSEL: J8.3
/XTAG/XTAG.TCK: J7.5, J8.9, R28.2, U11.1 (A1)
/XTAG/XTAG.TDI: J7.8, J8.13, R29.1
/XTAG/XTAG.TDO: J7.7, J8.5, JP10.2 (B)
/XTAG/XTAG.TMS: J7.6, J8.7, R27.2, U11.3 (A2)
/XTAG/XTAG.~DEBUG: J7.3, J8.11, JP9.2 (B)
/XTAGout.in0: J10.14; also elsewhere on the board
/XTAGout.in1: J10.18; also elsewhere on the board
/XTAGout.out0: J10.10; also elsewhere on the board
/XTAGout.out1: J10.6; also elsewhere on the board
/~DEBUG: J9.3, JP9.1 (A), JP15.1 (A), TP16.1; also elsewhere on the board
/~TRST: J7.2, J8.15; also elsewhere on the board
GND: C42.2, C43.2, J7.1, J7.4, J8.4, J8.8, J8.12, J8.16, J8.20, J9.1, J10.8, J10.12, J10.16, J10.20, R28.1, U11.2 (GND), U12.2 (GND); also elsewhere on the board
unnamed: J10.3, JP11.2 (B)
unnamed: J10.5, JP12.2 (B)
unnamed: J10.7, JP13.2 (B)
unnamed: J10.9, JP14.2 (B)
unnamed: J10.11, JP15.2 (B)
unnamed: J10.13, JP16.2 (B)
unnamed: J10.15, JP17.2 (B)
unnamed: R29.2, U12.4 (Z)
unnamed: RN9.1 (R1.1), U11.6 (Y1)
unnamed: RN9.2 (R2.1), U11.4 (Y2)

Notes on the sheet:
All one-way data flow wires has inverted direction in FEMALE connector to mate with MALE
Pin 5,7,9,13,15 must be connected for xCORE-200. Pin 11 for multi-PCB debug events. XTAG does not power any device.
TDI to pin 5 of the xSYS header TMS to pin 7 of the xSYS header TCK to pin 9 of the xSYS header DEBUG_N to pin 11 of the xSYS header TDO to pin 13 of the xSYS header
Stdout can be directed to JTAG, XLink or UART. JTAG disruptes realtime execution. The UART interface executes at a rate of 2MB/s
TDO from XMOS chip on this PCB
TDO from last XMOS chip in chain
A connected header or mini DIN will ground this net
XTAGin / xSYS header
XTAGout
Buffered TMS
Buffered TCK
Global ~RST
